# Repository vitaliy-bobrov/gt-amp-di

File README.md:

# GT Amp DI

GT Amp DI - custom modded SansAmp GT-2 circuit KiCad files.

The repository contains KiCad source files: schematic, PCB, BOM.

## Schematic

## PCB (3D preview)

## Interactive BOM

👉 [BOM](https://vitaliy-bobrov.github.io/gt-amp-di/)

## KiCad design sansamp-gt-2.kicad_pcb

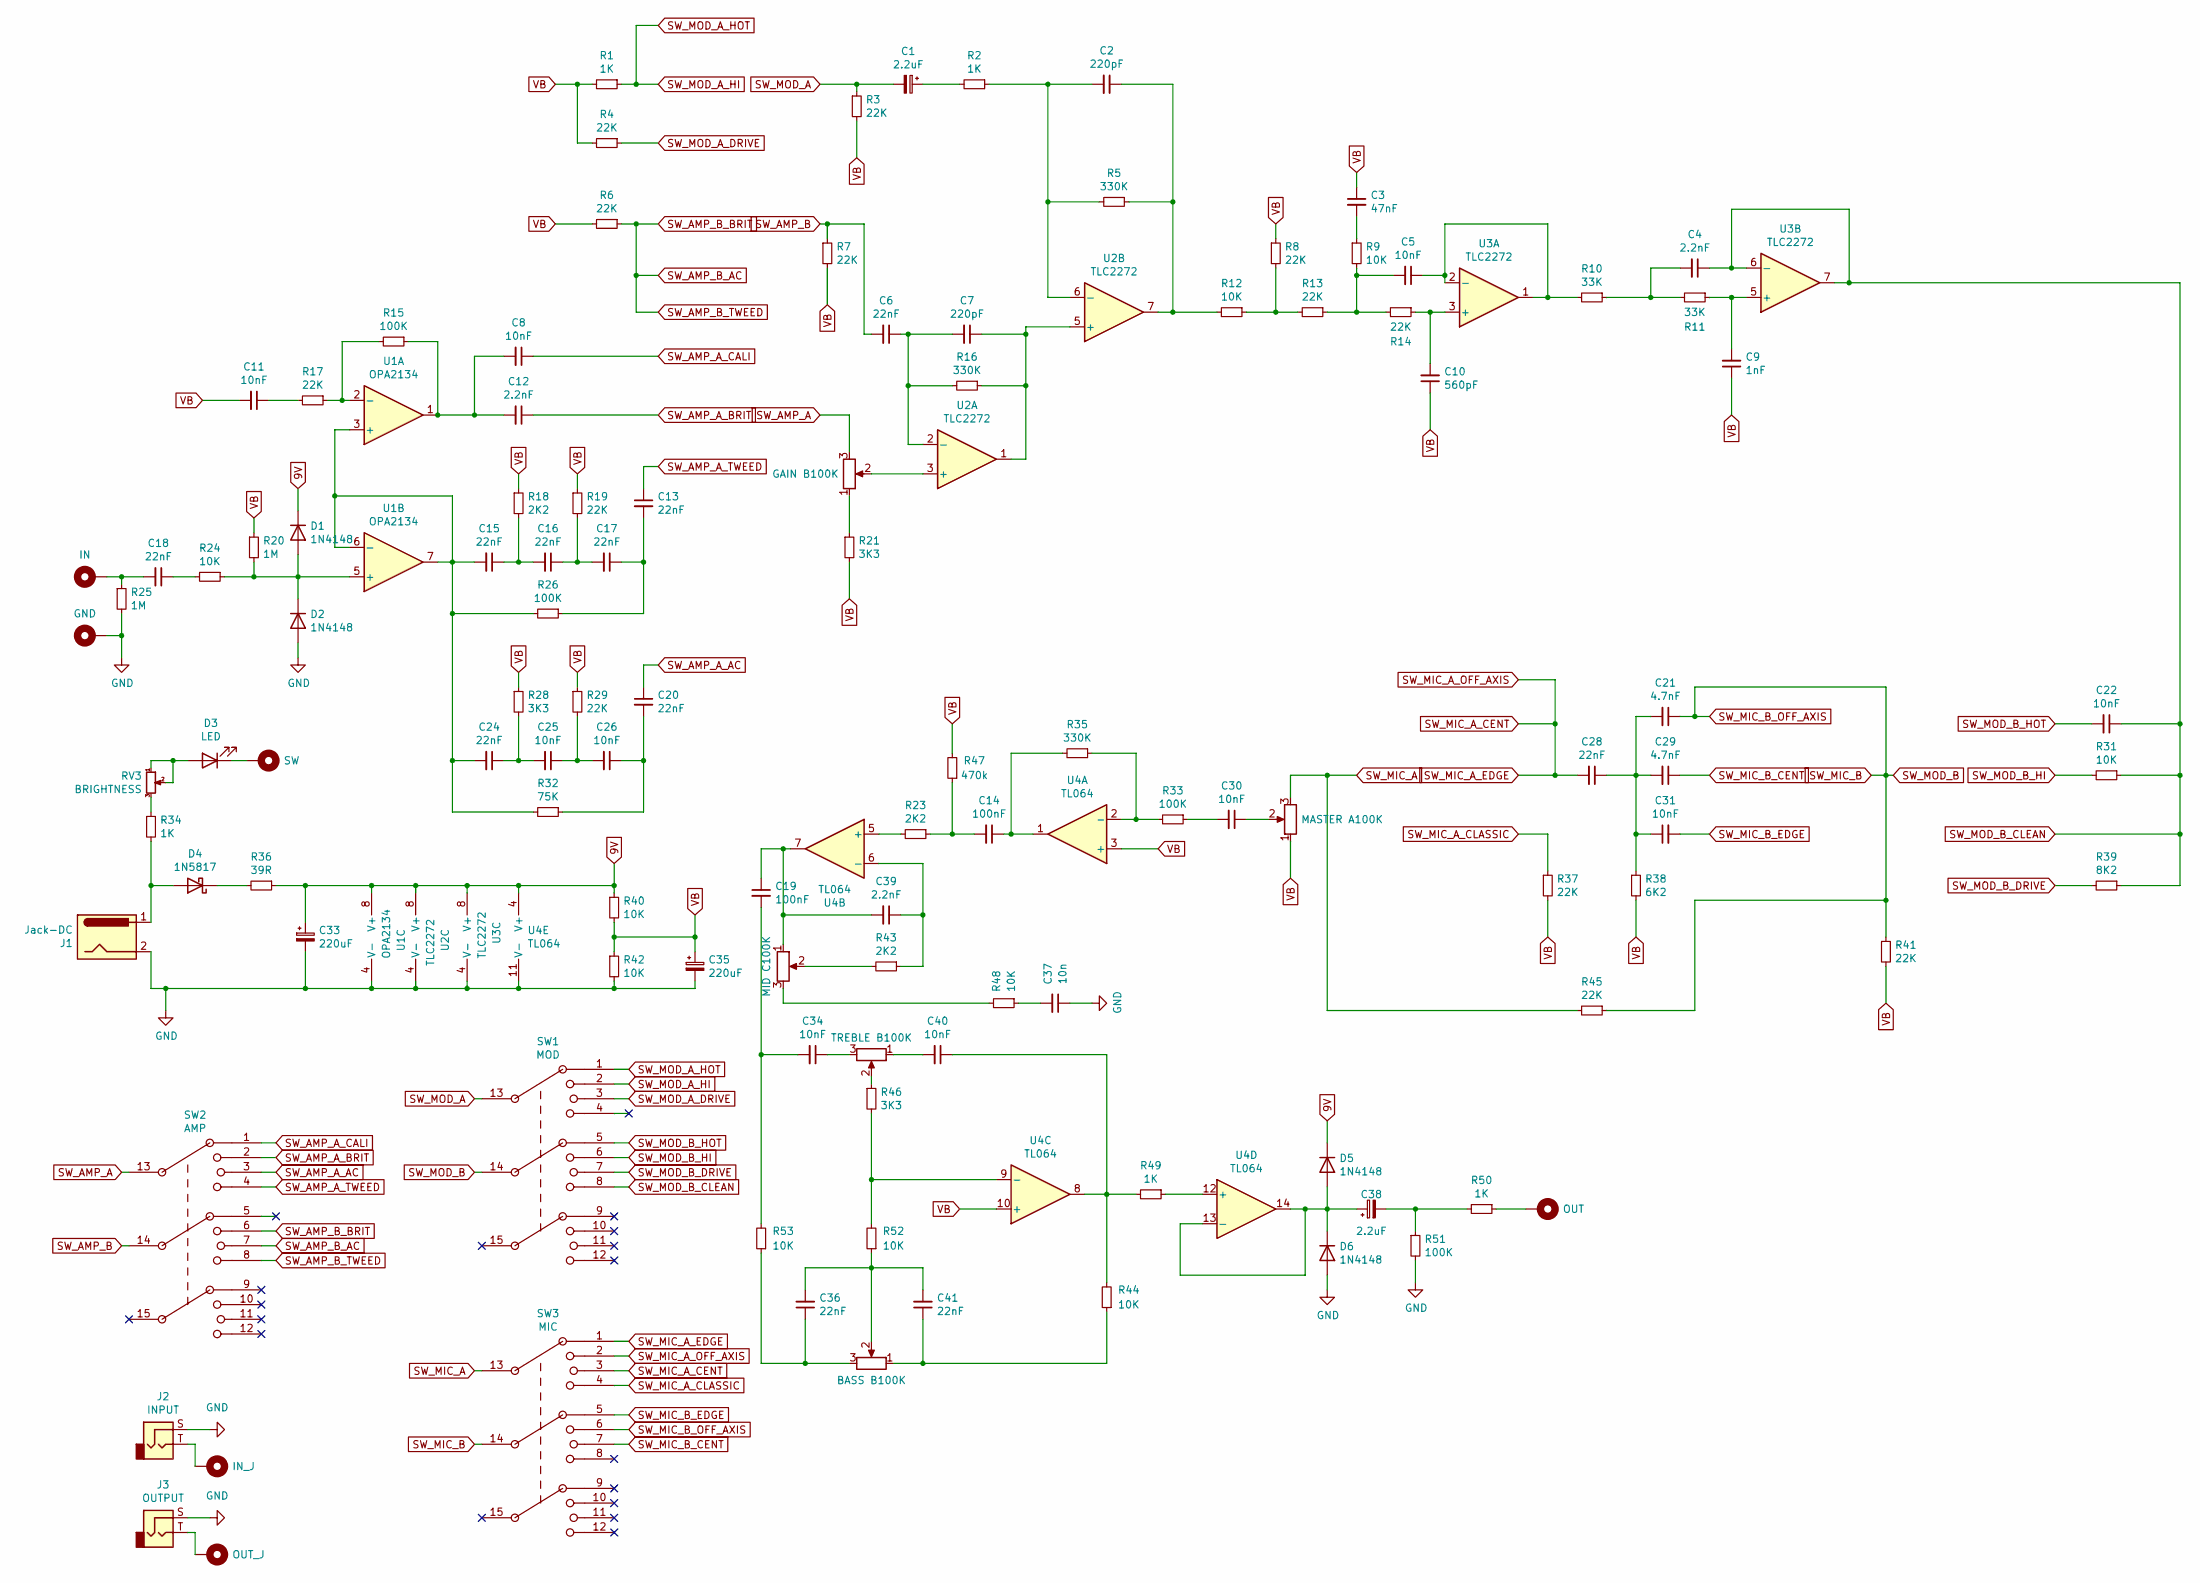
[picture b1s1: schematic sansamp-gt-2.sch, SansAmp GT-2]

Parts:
C1, C38: 2.2uF; 0502
C2, C7: 220pF; 0.2_22.MED
C3: 47nF; 0.2_22.SML
C4, C12, C39: 2.2nF; 0.2_22.SML
C5, C8, C11, C22, C25, C26, C30, C31, C34, C40: 10nF; 0.2_22.SML
C6, C13, C15, C16, C17, C18, C20, C24, C28, C36, C41: 22nF; 0.2_22.SML
C9: 1nF; 0.2_22.SML
C10: 560pF; 0.2_22.MED
C14, C19: 100nF; 0.2_22.SML
C21, C29: 4.7nF; 0.2_22.SML
C33, C35: 220uF; 0802
C37: 10n; 0.2_22.MED
D1, D2, D5, D6: 1N4148; DO35-2
D3: LED; 3MM_IO
D4: 1N5817; DO41-3
H1: IN; PAD1
H2: GND; PAD1
H3: SW; PAD1
H6: OUT; PAD1
H11: IN_J; PAD1
H12: OUT_J; PAD1
J1: Jack-DC; DC_JACK
J2: INPUT; TS_SW
J3: OUTPUT; TS_SW
R1, R2, R34, R49, R50: 1K; 0.3_22.B
R3, R4, R6, R7, R8, R13, R14, R17, R19, R29, R37, R41, R45: 22K; 0.3_22.B
R5, R16, R35: 330K; 0.3_22.B
R9, R12, R24, R31, R40, R42, R44, R48, R52, R53: 10K; 0.3_22.B
R10, R11: 33K; 0.3_22.B
R15, R26, R33, R51: 100K; 0.3_22.B
R18, R23, R43: 2K2; 0.3_22.B
R20, R25: 1M; 0.3_22.B
R21, R28, R46: 3K3; 0.3_22.B
R32: 75K; 0.3_22.B
R36: 39R; 0.3_22.B
R38: 6K2; 0.3_22.B
R39: 8K2; 0.3_22.B
R47: 470k; 0.3_22.B
RV1: GAIN B100K; 16MM_B.MOUNT
RV2: MID C100K; 16MM_B.MOUNT
RV3: BRIGHTNESS; TRIM1
RV4: MASTER A100K; 16MM_B.MOUNT
RV5: BASS B100K; 16MM_B.MOUNT
RV6: TREBLE B100K; 16MM_B.MOUNT
SW1: MOD; 2P4T.MINI_MODIF_KICAD
SW2: AMP; 2P4T.MINI_MODIF_KICAD
SW3: MIC; 2P4T.MINI_MODIF_KICAD
U1: OPA2134; DIP08
U2, U3: TLC2272; DIP08
U4: TL064; DIP14.1

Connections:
9V: C33.1, D1.1 (K), D5.1 (K), R36.1, R40.1, U1.8 (V+), U2.8 (V+), U3.8 (V+), U4.4 (V+)
GND: C33.2, C35.2, C37.1, D2.2 (A), D6.2 (A), H2.1, J1.2, J2.S, J3.S, R25.2, R42.2, R51.2, U1.4 (V-), U2.4 (V-), U3.4 (V-), U4.11 (V-)
unnamed: C1.1, R2.2
unnamed: C2.1, R5.1, R12.2, U2.7
unnamed: C2.2, R2.1, R5.2, U2.6 (-)
unnamed: C3.2, R9.1
unnamed: C4.2, R10.1, R11.2
unnamed: C5.1, R10.2, U3.1, U3.2 (-)
unnamed: C5.2, R9.2, R13.1, R14.2
unnamed: C6.1, C7.2, R16.2, U2.2 (-)
unnamed: C7.1, R16.1, U2.1, U2.5 (+)
unnamed: C9.2, R11.1, U3.5 (+)
unnamed: C10.2, R14.1, U3.3 (+)
unnamed: C11.1, R17.2
unnamed: C8.2, C12.2, R15.1, U1.1
unnamed: C13.2, C17.1, R26.1
unnamed: C14.1, R35.2, U4.1
unnamed: C14.2, R23.1, R47.1
unnamed: C15.1, C16.2, R18.2
unnamed: C15.2, C24.2, R26.2, R32.2, U1.3 (+), U1.6 (-), U1.7
unnamed: C16.1, C17.2, R19.2
unnamed: C18.1, R24.2
unnamed: C18.2, H1.1, R25.1
unnamed: C19.1, C39.2, RV2.1, U4.7
unnamed: C19.2, C34.2, R53.2
unnamed: C20.2, C26.1, R32.1
unnamed: C21.2, C28.1, C29.2, C31.1, R38.1
unnamed: C24.1, C25.2, R28.2
unnamed: C25.1, C26.2, R29.2
unnamed: C30.1, RV4.2
unnamed: C30.2, R33.1
unnamed: C34.1, RV6.3
unnamed: C36.1, R53.1, RV5.3
unnamed: C36.2, C41.2, R52.1, RV5.2
unnamed: C37.2, R48.1
unnamed: C38.1, D5.2 (A), D6.1 (K), U4.13 (-), U4.14
unnamed: C38.2, R50.2, R51.1
unnamed: C39.1, R43.1, U4.6 (-)
unnamed: C40.1, R44.2, R49.2, U4.8
unnamed: C40.2, RV6.1
unnamed: C41.1, R44.1, RV5.1
unnamed: D1.2 (A), D2.1 (K), R20.2, R24.1, U1.5 (+)
unnamed: D3.1 (K), H3.1
unnamed: D3.2 (A), RV3.1, RV3.2
unnamed: D4.1 (K), R36.2
unnamed: D4.2 (A), J1.1, R34.2
unnamed: H6.1, R50.1
unnamed: H11.1, J2.T
unnamed: H12.1, J3.T
unnamed: R8.2, R12.1, R13.2
unnamed: R15.2, R17.1, U1.2 (-)
unnamed: R21.1, RV1.1
unnamed: R23.2, U4.5 (+)
unnamed: R33.2, R35.1, U4.2 (-)
unnamed: R34.1, RV3.3
unnamed: R43.2, RV2.2
unnamed: R46.1, RV6.2
unnamed: R46.2, R52.2, U4.9 (-)
unnamed: R48.2, RV2.3
unnamed: R49.1, U4.12 (+)
unnamed: RV1.2, U2.3 (+)
SW_AMP_A: RV1.3, SW2.13
SW_AMP_A_AC: C20.1, SW2.3
SW_AMP_A_BRIT: C12.1, SW2.2
SW_AMP_A_CALI: C8.1, SW2.1
SW_AMP_A_TWEED: C13.1, SW2.4
SW_AMP_B: C6.2, R7.1, SW2.14
SW_AMP_B_AC: R6.1, SW2.6, SW2.7, SW2.8
SW_MIC_A: R45.2, RV4.3, SW3.13
SW_MIC_A_CENT: C28.2, SW3.1, SW3.2, SW3.3
SW_MIC_A_CLASSIC: R37.1, SW3.4
SW_MIC_B: C21.1, R41.1, R45.1, SW1.14, SW3.6, SW3.14
SW_MIC_B_CENT: C29.1, SW3.7
SW_MIC_B_EDGE: C31.2, SW3.5
SW_MOD_A: C1.2, R3.1, SW1.13
SW_MOD_A_DRIVE: R4.1, SW1.3
SW_MOD_A_HI: R1.1, SW1.1, SW1.2
SW_MOD_B_CLEAN: C4.1, C22.1, R31.1, R39.1, SW1.8, U3.6 (-), U3.7
SW_MOD_B_DRIVE: R39.2, SW1.7
SW_MOD_B_HI: R31.2, SW1.6
SW_MOD_B_HOT: C22.2, SW1.5
VB: C3.1, C9.1, C10.1, C11.2, C35.1, R1.2, R3.2, R4.2, R6.2, R7.2, R8.1, R18.1, R19.1, R20.1, R21.2, R28.1, R29.1, R37.2, R38.2, R40.2, R41.2, R42.1, R47.2, RV4.1, U4.3 (+), U4.10 (+)

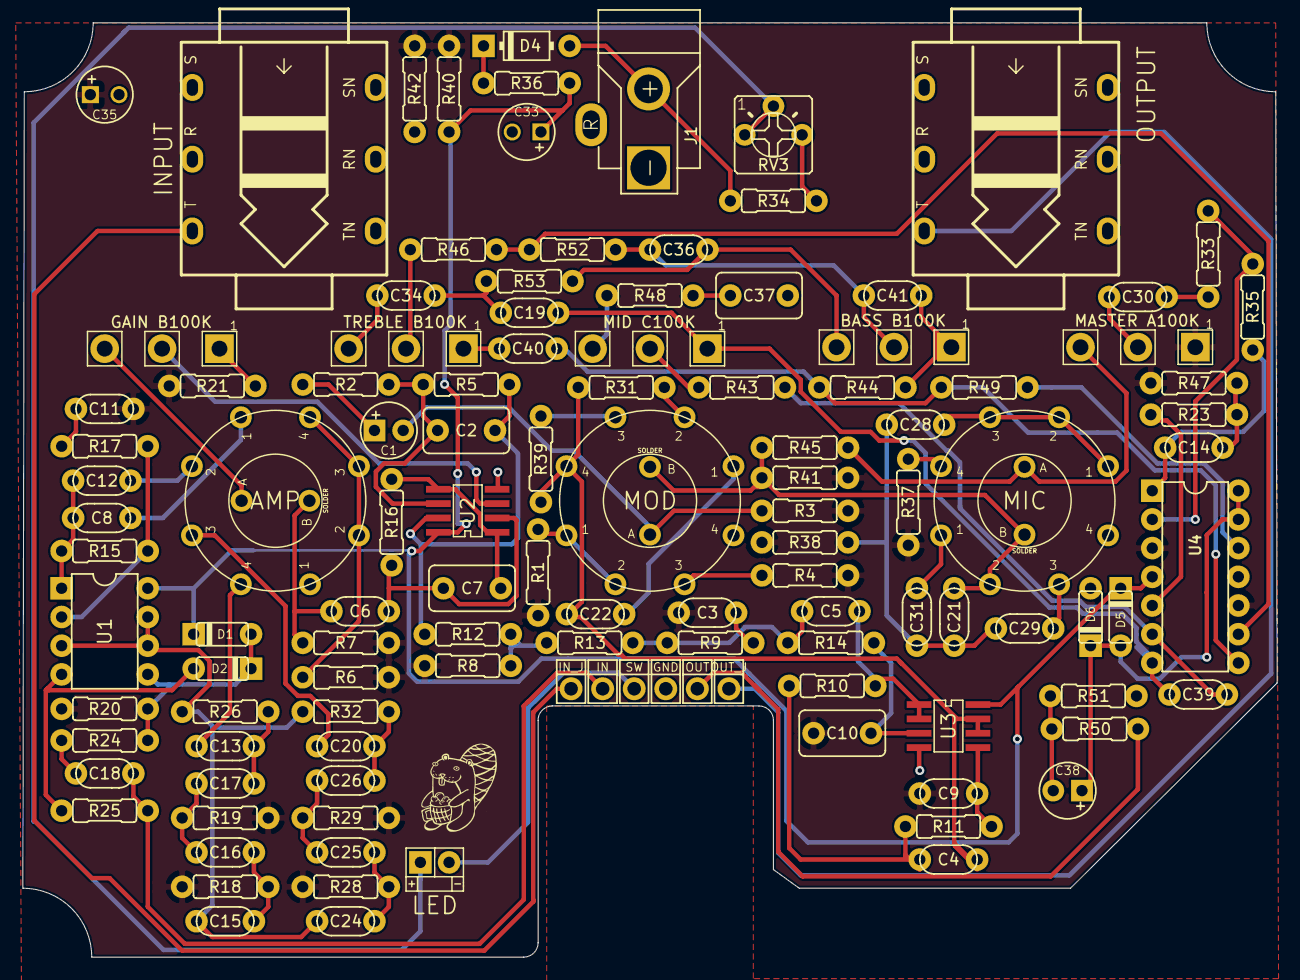
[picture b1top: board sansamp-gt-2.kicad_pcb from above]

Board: 2 copper layers, 111.0 x 82.7 mm, 116 parts (0 on the bottom side), 82 nets.

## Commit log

2021-03-17 v2.0
